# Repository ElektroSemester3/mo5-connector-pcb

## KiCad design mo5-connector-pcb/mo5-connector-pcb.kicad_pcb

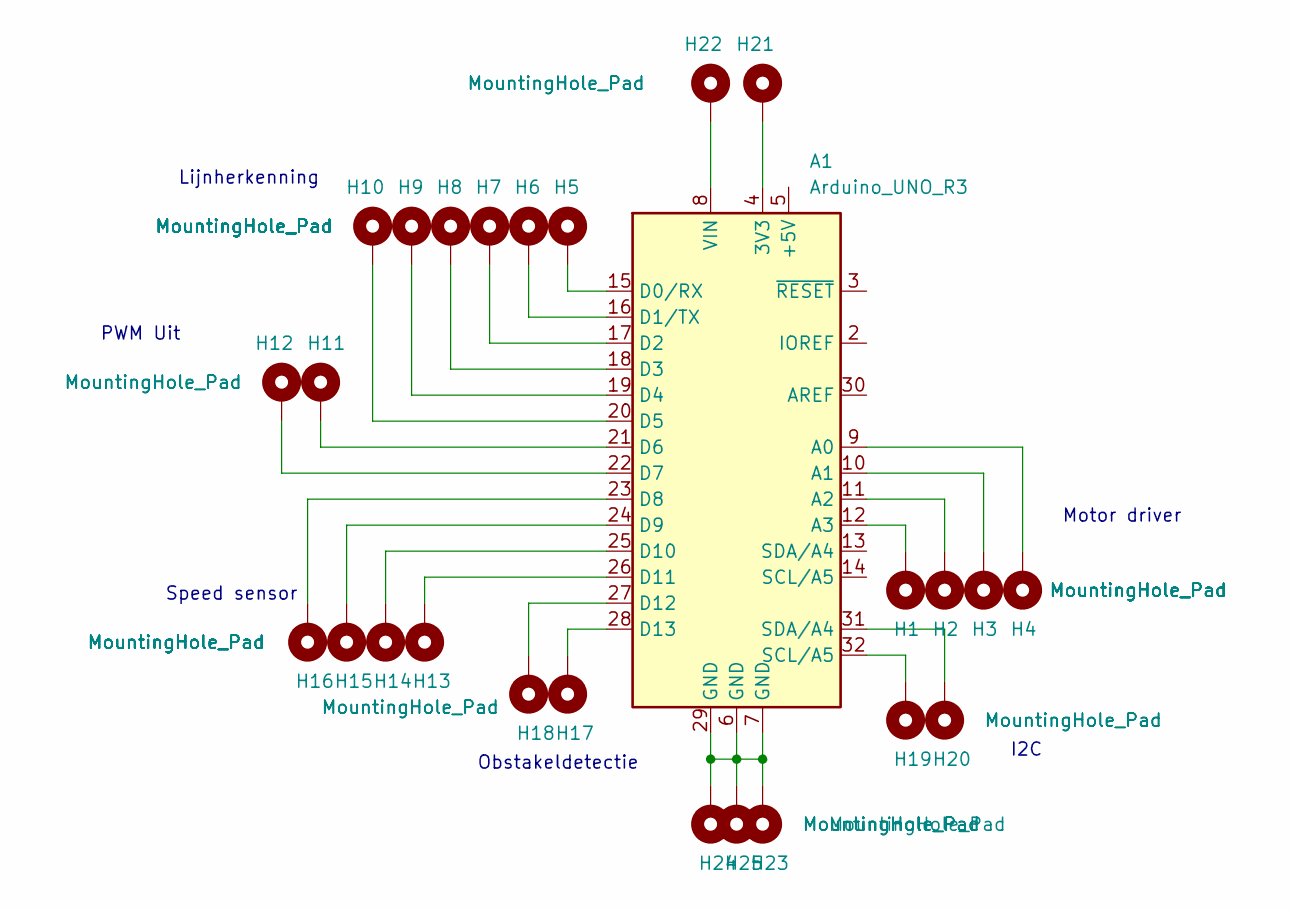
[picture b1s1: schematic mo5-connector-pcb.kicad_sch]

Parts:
A1: Arduino_UNO_R3
H1, H2, H3, H4, H5, H6, H7, H8, H9, H10, H11, H12, H13, H14, H15, H16, H17, H18, H19, H20: MountingHole_Pad; SolderWirePad_1x01_SMD_1x2mm
H21, H22, H23, H24, H25: MountingHole_Pad; SolderWirePad_1x01_SMD_5x10mm

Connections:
unnamed: A1.4 (3V3), H21.1
unnamed: A1.9 (A0), H4.1
unnamed: A1.10 (A1), H3.1
unnamed: A1.11 (A2), H2.1
unnamed: A1.12 (A3), H1.1
unnamed: A1.15 (D0/RX), H5.1
unnamed: A1.16 (D1/TX), H6.1
unnamed: A1.17 (D2), H7.1
unnamed: A1.18 (D3), H8.1
unnamed: A1.19 (D4), H9.1
unnamed: A1.20 (D5), H10.1
unnamed: A1.21 (D6), H11.1
unnamed: A1.22 (D7), H12.1
unnamed: A1.23 (D8), H16.1
unnamed: A1.24 (D9), H15.1
unnamed: A1.25 (D10), H14.1
unnamed: A1.26 (D11), H13.1
unnamed: A1.27 (D12), H18.1
unnamed: A1.28 (D13), H17.1
unnamed: A1.6 (GND), A1.7 (GND), A1.29 (GND), H23.1, H24.1, H25.1
unnamed: A1.32 (SCL/A5), H19.1
unnamed: A1.31 (SDA/A4), H20.1
unnamed: A1.8 (VIN), H22.1

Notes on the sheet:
PWM Uit
Obstakeldetectie
I2C
Motor driver
Lijnherkenning
Speed sensor

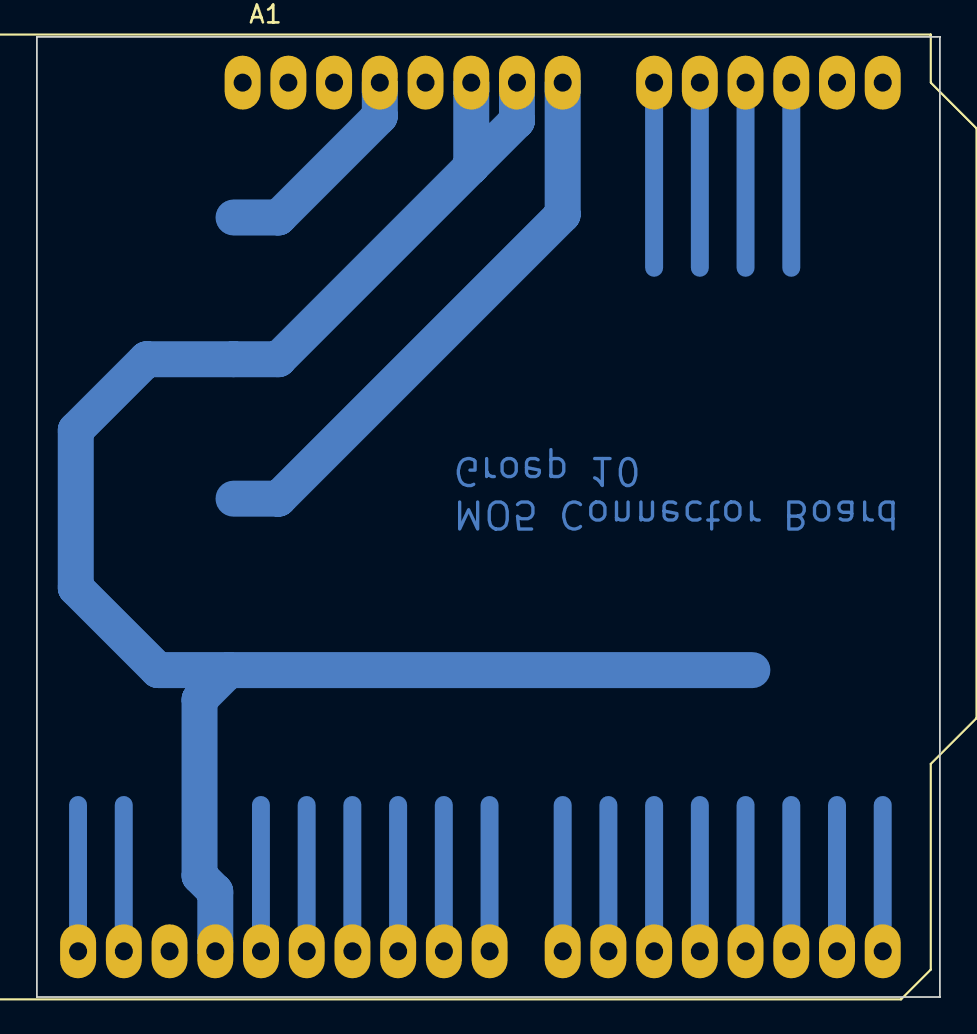
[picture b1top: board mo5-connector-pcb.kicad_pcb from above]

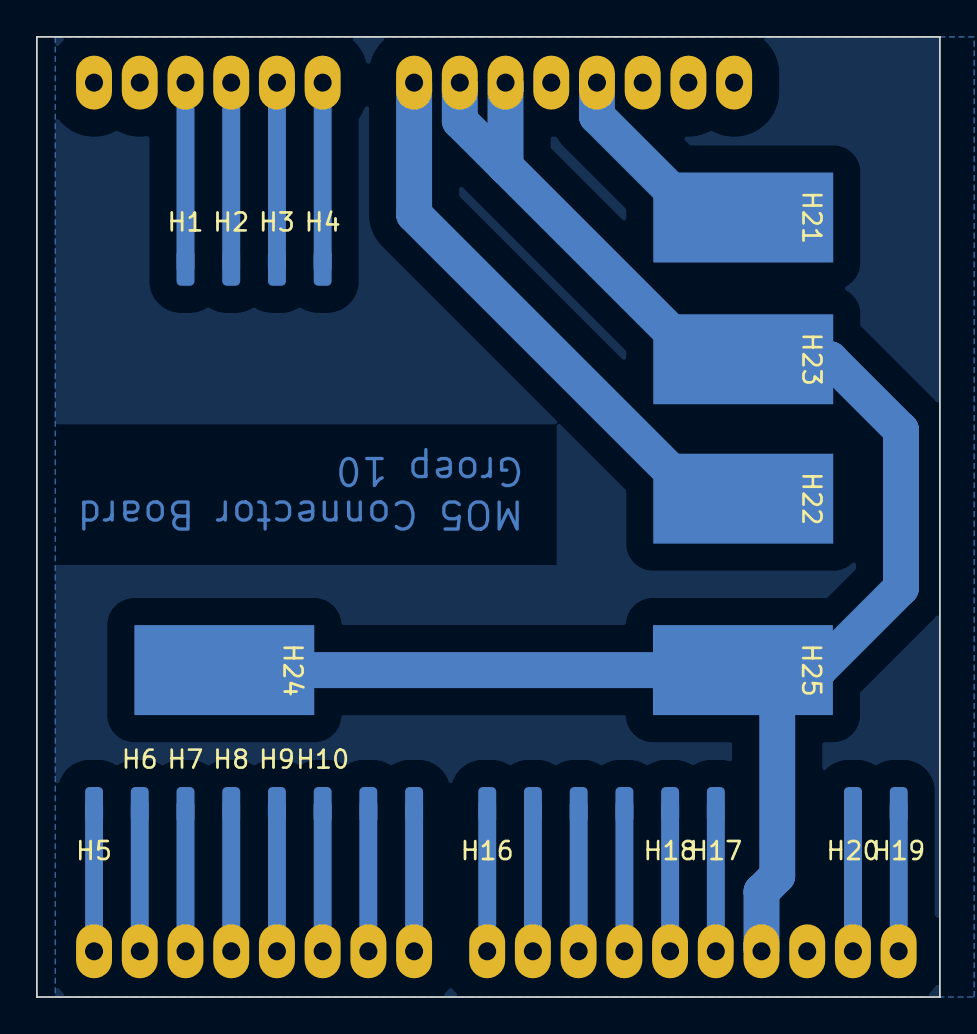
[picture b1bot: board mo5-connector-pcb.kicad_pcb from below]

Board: 2 copper layers, 50.2 x 53.3 mm, 26 parts (25 on the bottom side), 23 nets.

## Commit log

2024-01-16 Gemaakt
2024-01-16 Prepare for production
